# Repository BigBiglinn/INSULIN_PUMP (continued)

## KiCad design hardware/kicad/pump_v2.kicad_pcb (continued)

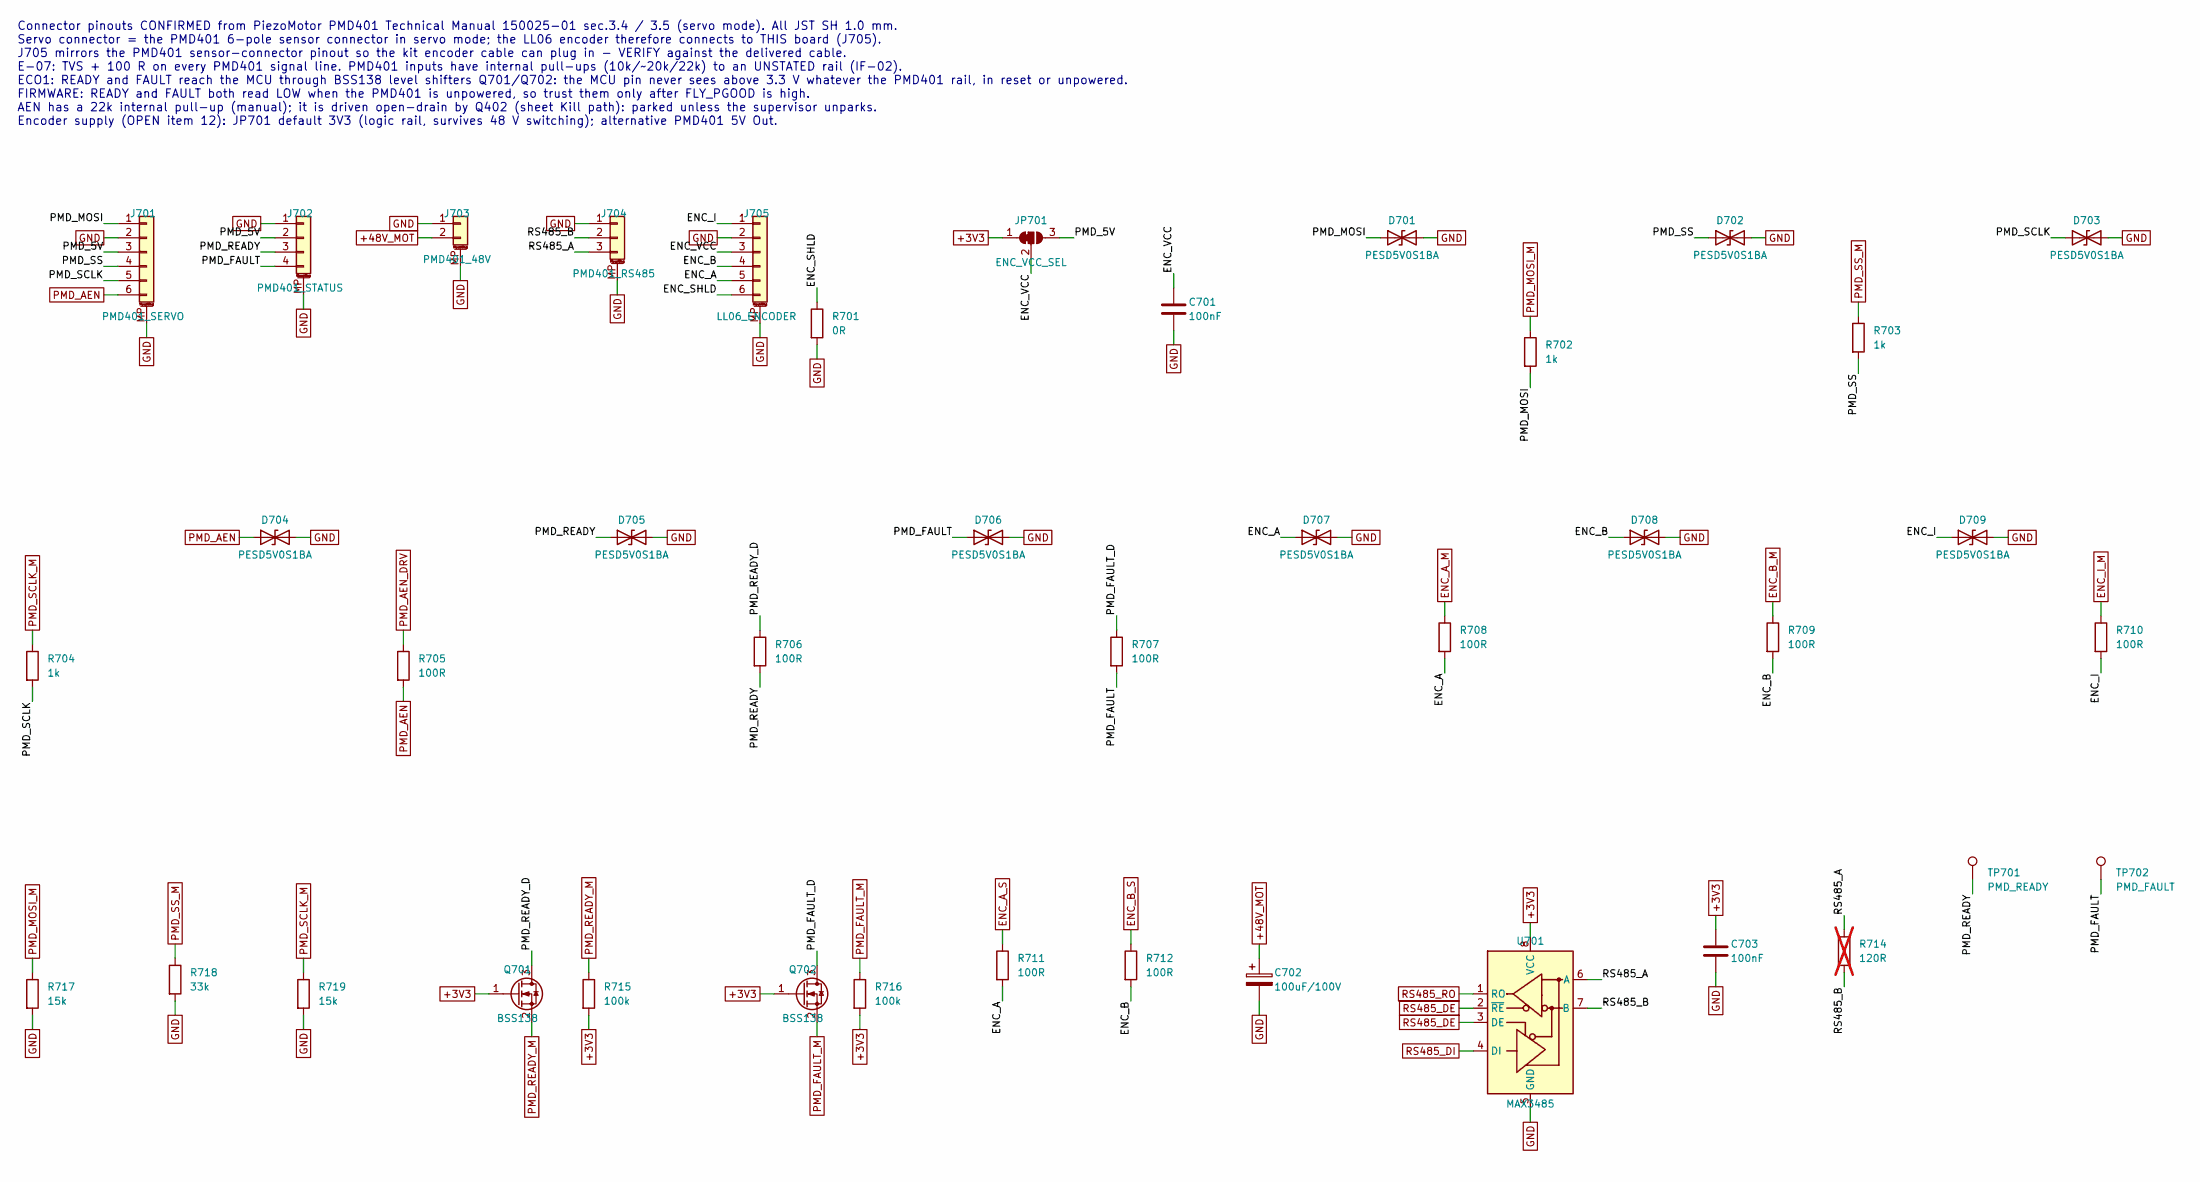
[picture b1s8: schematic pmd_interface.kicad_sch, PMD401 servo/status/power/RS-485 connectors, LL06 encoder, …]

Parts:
C701, C703: 100nF; C_0603_1608Metric
C702: 100uF/100V; CP_Radial_D12.5mm_P5.00mm
D701, D702, D703, D704, D705, D706, D707, D708, D709: PESD5V0S1BA; D_SOD-323; MPN Nexperia PESD5V0S1BA,115
J701: PMD401_SERVO; JST_SH_SM06B-SRSS-TB_1x06-1MP_P1.00mm_Horizontal; MPN JST SM06B-SRSS-TB
J702: PMD401_STATUS; JST_SH_SM04B-SRSS-TB_1x04-1MP_P1.00mm_Horizontal; MPN JST SM04B-SRSS-TB
J703: PMD401_48V; JST_SH_SM02B-SRSS-TB_1x02-1MP_P1.00mm_Horizontal; MPN JST SM02B-SRSS-TB
J704: PMD401_RS485; JST_SH_SM03B-SRSS-TB_1x03-1MP_P1.00mm_Horizontal; MPN JST SM03B-SRSS-TB
J705: LL06_ENCODER; JST_SH_SM06B-SRSS-TB_1x06-1MP_P1.00mm_Horizontal; MPN JST SM06B-SRSS-TB
JP701: ENC_VCC_SEL; SolderJumper-3_P1.3mm_Bridged12_RoundedPad1.0x1.5mm_NumberL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
Q701, Q702: BSS138; SOT-23; MPN BSS138 (e.g. Nexperia BSS138P)
R701: 0R; R_0603_1608Metric
R702, R703, R704: 1k; R_0603_1608Metric
R705, R706, R707, R708, R709, R710, R711, R712: 100R; R_0603_1608Metric
R714: 120R; R_0603_1608Metric; not fitted
R715, R716: 100k; R_0603_1608Metric
R717, R719: 15k; R_0603_1608Metric
R718: 33k; R_0603_1608Metric
TP701: PMD_READY; TestPoint_Pad_D1.0mm
TP702: PMD_FAULT; TestPoint_Pad_D1.0mm
U701: MAX3485; SOIC-8_3.9x4.9mm_P1.27mm; MPN MAX3485 SOIC-8 (suffix TBD)

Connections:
+3V3: C703.1, JP701.1 (A), Q701.1 (G), Q702.1 (G), R715.2, R716.2, U701.8 (VCC); also elsewhere on the board
/PMD401 & encoder interface/ENC_A: D707.1 (A1), J705.5, R708.2, R711.2
/PMD401 & encoder interface/ENC_B: D708.1 (A1), J705.4, R709.2, R712.2
/PMD401 & encoder interface/ENC_I: D709.1 (A1), J705.1, R710.2
/PMD401 & encoder interface/ENC_SHLD: J705.6, R701.1
/PMD401 & encoder interface/ENC_VCC: C701.1, J705.3, JP701.2 (C)
/PMD401 & encoder interface/PMD_5V: J701.3, J702.2, JP701.3 (B)
/PMD401 & encoder interface/PMD_FAULT: D706.1 (A1), J702.4, R707.2, TP702.1
/PMD401 & encoder interface/PMD_FAULT_D: Q702.3 (D), R707.1
/PMD401 & encoder interface/PMD_MOSI: D701.1 (A1), J701.1, R702.2
/PMD401 & encoder interface/PMD_READY: D705.1 (A1), J702.3, R706.2, TP701.1
/PMD401 & encoder interface/PMD_READY_D: Q701.3 (D), R706.1
/PMD401 & encoder interface/PMD_SCLK: D703.1 (A1), J701.5, R704.2
/PMD401 & encoder interface/PMD_SS: D702.1 (A1), J701.4, R703.2
/PMD401 & encoder interface/RS485_A: J704.3, R714.1, U701.6 (A)
/PMD401 & encoder interface/RS485_B: J704.2, R714.2, U701.7 (B)
ENC_A_M: R708.1; also elsewhere on the board
ENC_A_S: R711.1; also elsewhere on the board
ENC_B_M: R709.1; also elsewhere on the board
ENC_B_S: R712.1; also elsewhere on the board
ENC_I_M: R710.1; also elsewhere on the board
PMD_AEN: D704.1 (A1), J701.6, R705.2; also elsewhere on the board
PMD_AEN_DRV: R705.1; also elsewhere on the board
PMD_FAULT_M: Q702.2 (S), R716.1; also elsewhere on the board
PMD_MOSI_M: R702.1, R717.1; also elsewhere on the board
PMD_READY_M: Q701.2 (S), R715.1; also elsewhere on the board
PMD_SCLK_M: R704.1, R719.1; also elsewhere on the board
PMD_SS_M: R703.1, R718.1; also elsewhere on the board
RS485_DE: U701.2 (~RE), U701.3 (DE); also elsewhere on the board
RS485_DI: U701.4 (DI); also elsewhere on the board
RS485_RO: U701.1 (RO); also elsewhere on the board

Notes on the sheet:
Connector pinouts CONFIRMED from PiezoMotor PMD401 Technical Manual 150025-01 sec.3.4 / 3.5 (servo mode). All JST SH 1.0 mm. Servo connector = the PMD401 6-pole sensor connector in servo mode; the LL06 encoder therefore connects to THIS board (J705). J705 mirrors the PMD401 sensor-connector pinout 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

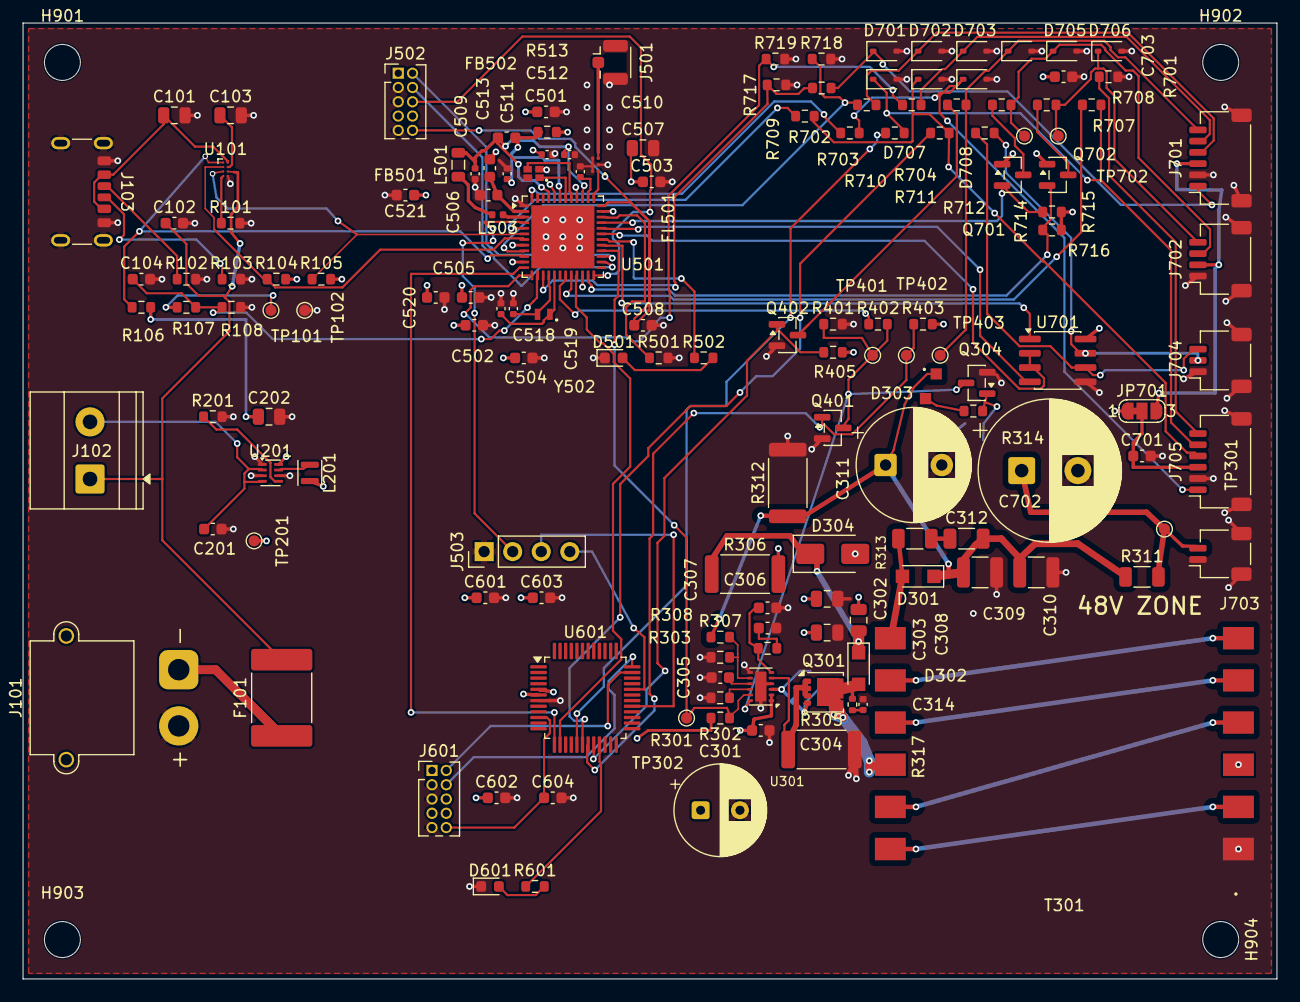
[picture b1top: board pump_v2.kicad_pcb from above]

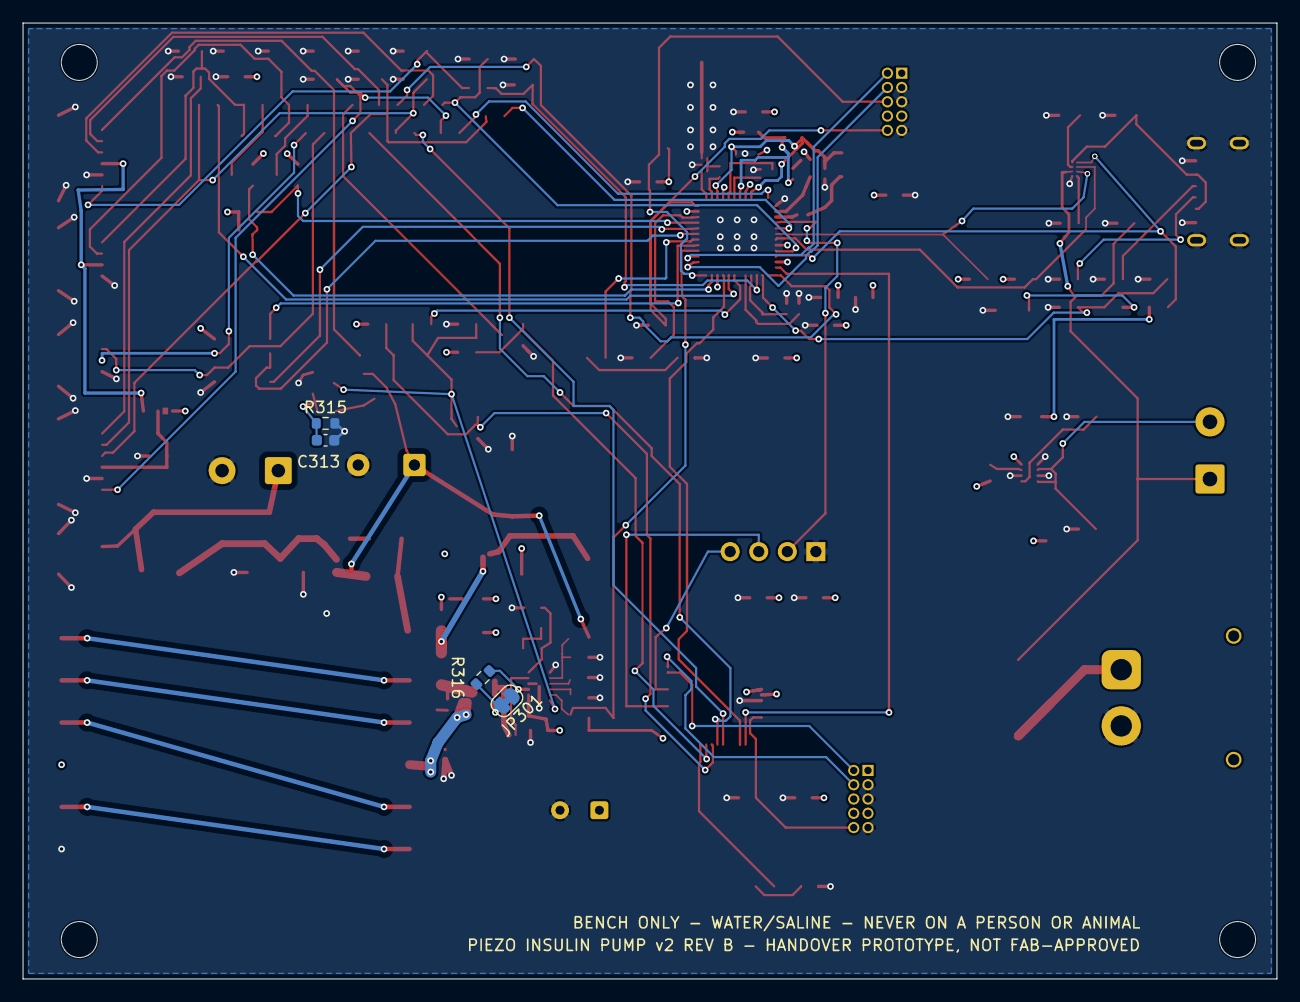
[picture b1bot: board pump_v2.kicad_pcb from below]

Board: 4 copper layers, 111.5 x 85.0 mm, 158 parts (4 on the bottom side), 101 nets.

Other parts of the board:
C313: 10nF; C_0603_1608Metric
C314: TBD; C_0402_1005Metric
D303: BZX84B51; SOT-23_Zener_A1_K3
D304: SMAJ15A; D_SMA
JP301: BRIDGED; SolderJumper-2_P1.3mm_Bridged_RoundedPad1.0x1.5mm
Q304: BSS138; SOT-23
R314: 1k; R_0603_1608Metric
R315: 10k; R_0603_1608Metric
R316: TBD; R_0603_1608Metric
R317: TBD; R_0402_1005Metric

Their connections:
/48V flyback/FLY_CLAMP: D304.1; also elsewhere on the board
/48V flyback/FLY_DSNB: C314.1, R317.2
/48V flyback/OVP_G: C313.1, Q304.1, R314.2, R315.1
/48V flyback/OVP_K: D303.2, R314.1
FLY_EN: Q304.3; also elsewhere on the board

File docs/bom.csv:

"Refs","Value","Footprint","MPN","Status","Qty","DNP"
"C101","2.2uF/25V","Capacitor_SMD:C_0805_2012Metric","","DS","1",""
"C102","1uF/10V","Capacitor_SMD:C_0603_1608Metric","","DS","1",""
"C103,C202","10uF/10V","Capacitor_SMD:C_0805_2012Metric","","DS","2",""
"C104","100nF","Capacitor_SMD:C_0603_1608Metric","","CALC","1",""
"C201","4.7uF/10V","Capacitor_SMD:C_0603_1608Metric","","DS","1",""
"C301","220uF/16V","Capacitor_THT:CP_Radial_D8.0mm_P3.50mm","","DECIDED","1",""
"C302,C303","10uF/10V X5R","Capacitor_SMD:C_0805_2012Metric","","CALC","2",""
"C304","2.2uF/10V","Capacitor_SMD:C_0603_1608Metric","","DS","1",""
"C305","4.7uF/10V X5R","Capacitor_SMD:C_0603_1608Metric","","CALC","1",""
"C306","180nF","Capacitor_SMD:C_0603_1608Metric","","CALC","1",""
"C307","3.3nF","Capacitor_SMD:C_0603_1608Metric","","CALC","1",""
"C308","470nF/50V X7R","Capacitor_SMD:C_0805_2012Metric","","CALC","1",""
"C309,C310","2.2uF/100V X7R","Capacitor_SMD:C_1210_3225Metric","","CALC","2",""
"C311","47uF/100V","Capacitor_THT:CP_Radial_D10.0mm_P5.00mm","","DECIDED","1",""
"C312","100pF/250V C0G","Capacitor_SMD:C_1206_3216Metric","","CALC","1",""
"C501,C502,C503,C504,C505,C506,C508,C601,C602,C604,C701,C703","100nF","Capacitor_SMD:C_0603_1608Metric","","ASSUMED","12",""
"C507,C603","4.7uF","Capacitor_SMD:C_0603_1608Metric","","ASSUMED","2",""
"C509,C510,C511,C512,C513","TBD","Capacitor_SMD:C_0603_1608Metric","","PLACEHOLDER","5",""
"C514,C515,C516,C517,C518,C519","TBD","Capacitor_SMD:C_0402_1005Metric","","PLACEHOLDER","6","DNP"
"C702","100uF/100V","Capacitor_THT:CP_Radial_D12.5mm_P5.00mm","","DECIDED","1",""
"D301","PNE20010ER","Diode_SMD:Nexperia_CFP3_SOD-123W","Nexperia PNE20010ER","DS","1",""
"D302","PMEG10020ELR","Diode_SMD:Nexperia_CFP3_SOD-123W","Nexperia PMEG10020ELR","DS","1",""
"D501","LED_GRN","LED_SMD:LED_0603_1608Metric","","ASSUMED","1",""
"D601","LED_RED","LED_SMD:LED_0603_1608Metric","","ASSUMED","1",""
"D701,D702,D703,D704,D705,D706,D707,D708,D709","TVS_5V_TBD","Diode_SMD:D_SOD-323","","TBD","9",""
"F101","5A","Fuse:Fuse_2920_7451Metric","","TBD","1",""
"J101","BATTERY_1S","Connector_AMASS:AMASS_XT30PW-M_1x02_P2.50mm_Horizontal","AMASS XT30PW-M","ASSUMED","1",""
"J102","MASTER_SW_EXT","TerminalBlock_Phoenix:TerminalBlock_Phoenix_MKDS-1,5-2-5.08_1x02_P5.08mm_Horizontal","","ASSUMED","1",""
"J103","USB_C_PWR","Connector_USB:USB_C_Receptacle_GCT_USB4125-xx-x_6P_TopMnt_Horizontal","GCT USB4125","ASSUMED","1",""
"J501","U.FL","Connector_Coaxial:U.FL_Hirose_U.FL-R-SMT-1_Vertical","Hirose U.FL-R-SMT-1","ASSUMED","1",""
"J502,J601","SWD_10pin","Connector_PinHeader_1.27mm:PinHeader_2x05_P1.27mm_Vertical","","ASSUMED","2",""
"J503","CONSOLE","Connector_PinHeader_2.54mm:PinHeader_1x04_P2.54mm_Vertical","","ASSUMED","1",""
"J701","PMD401_SERVO","Connector_JST:JST_SH_SM06B-SRSS-TB_1x06-1MP_P1.00mm_Horizontal","JST SM06B-SRSS-TB","DS","1",""
"J702","PMD401_STATUS","Connector_JST:JST_SH_SM04B-SRSS-TB_1x04-1MP_P1.00mm_Horizontal","JST SM04B-SRSS-TB","DS","1",""
"J703","PMD401_48V","Connector_JST:JST_SH_SM02B-SRSS-TB_1x02-1MP_P1.00mm_Horizontal","JST SM02B-SRSS-TB","DS","1",""
"J704","PMD401_RS485","Connector_JST:JST_SH_SM03B-SRSS-TB_1x03-1MP_P1.00mm_Horizontal","JST SM03B-SRSS-TB","DS","1",""
"J705","LL06_ENCODER","Connector_JST:JST_SH_SM06B-SRSS-TB_1x06-1MP_P1.00mm_Horizontal","JST SM06B-SRSS-TB","ASSUMED","1",""
"JP701","ENC_VCC_SEL","Jumper:SolderJumper-3_P1.3mm_Bridged12_RoundedPad1.0x1.5mm_NumberLabels","","ASSUMED","1",""
"L201","2.2uH","Inductor_SMD:L_0603_1608Metric","","DS","1",""
"L501","L_SMPS_TBD","Inductor_SMD:L_0805_2012Metric","","PLACEHOLDER","1",""
"L502","TBD","Inductor_SMD:L_0402_1005Metric","","PLACEHOLDER","1",""
"Q301","CSD16340Q3","Package_SON:VSON-8_3.3x3.3mm_P0.65mm_NexFET","TI CSD16340Q3","DS","1",""
"Q302","PMOS_TBD","Package_TO_SOT_SMD:SOT-223-3_TabPin2","","PLACEHOLDER","1","DNP"
"Q303","NMOS_TBD","Package_TO_SOT_SMD:SOT-223-3_TabPin2","","PLACEHOLDER","1","DNP"
"Q401","BSS138","Package_TO_SOT_SMD:SOT-23","BSS138","DECIDED","1",""
"Q402","BSS138","Package_TO_SOT_SMD:SOT-23","BSS138 (e.g. Nexperia BSS138P)","DECIDED","1",""
"R101,R104,R105,R106","10k","Resistor_SMD:R_0603_1608Metric","","DS","4",""
"R102,R103","5.1k","Resistor_SMD:R_0603_1608Metric","","ASSUMED","2",""
"R107,R108","1M 1%","Resistor_SMD:R_0603_1608Metric","","CALC","2",""
"R201","267k 1%","Resistor_SMD:R_0603_1608Metric","","DS","1",""
"R301","73.2k 1%","Resistor_SMD:R_0603_1608Metric","","CALC","1",""
"R302","100k","Resistor_SMD:R_0603_1608Metric","","ASSUMED","1",""
"R303","3.01k 1%","Resistor_SMD:R_0603_1608Metric","","CALC","1",""
"R305","22m 1% 1W","Resistor_SMD:R_2512_6332Metric","","CALC","1",""
"R306","220R 1W","Resistor_SMD:R_2512_6332Metric","","CALC","1",""
"R307","470k 1%","Resistor_SMD:R_0603_1608Metric","","CALC","1",""
"R308","10k 1%","Resistor_SMD:R_0603_1608Metric","","CALC","1",""
"R309,R310","TBD","Resistor_SMD:R_0603_1608Metric","","PLACEHOLDER","2","DNP"
"R311","0R","Resistor_SMD:R_1206_3216Metric","","ASSUMED","1",""
"R312","TBD","Resistor_SMD:R_2512_6332Metric","","PLACEHOLDER","1","DNP"
"R313","220R 1206","Resistor_SMD:R_1206_3216Metric","","CALC","1",""
"R401","4.7k","Resistor_SMD:R_0603_1608Metric","","DECIDED","1",""
"R402","1k","Resistor_SMD:R_0603_1608Metric","","DECIDED","1",""
"R403,R405","10k","Resistor_SMD:R_0603_1608Metric","","DECIDED","2",""
"R501","10k","Resistor_SMD:R_0603_1608Metric","","ASSUMED","1",""
"R502,R601","1k","Resistor_SMD:R_0603_1608Metric","","ASSUMED","2",""
"R510,R511,R512,R513","0R_VERIFY","Resistor_SMD:R_0603_1608Metric","","PLACEHOLDER","4","DNP"
"R701","0R","Resistor_SMD:R_0603_1608Metric","","ASSUMED","1",""
"R702,R703,R704,R705,R706,R707,R708,R709,R710,R711,R712","100R","Resistor_SMD:R_0603_1608Metric","","DECIDED","11",""
"R714","120R","Resistor_SMD:R_0603_1608Metric","","ASSUMED","1","DNP"
"T301","XFMR_TBD","pump_v2:XFMR_PLACEHOLDER_4P","","PLACEHOLDER","1",""
"U101","BQ25188YBGR","pump_v2:TI_YBG0008_DSBGA-8_P0.4mm","BQ25188YBGR","DECIDED","1",""
"U201","TPS62840DLCR","Package_SON:Texas_VSON-HR-8_1.5x2mm_P0.5mm","TPS62840DLCR","DECIDED","1",""
"U301","LM51551DSSR","Package_SON:WSON-12-1EP_3x2mm_P0.5mm_EP1x2.65","LM51551DSSR","DECIDED","1",""
"U501","STM32WBA55CGUx","Package_DFN_QFN:QFN-48-1EP_7x7mm_P0.5mm_EP5.6x5.6mm","STM32WBA55CGU6 (temp suffix TBD)","DECIDED","1",""
"U601","STM32C031C6Tx","Package_QFP:LQFP-48_7x7mm_P0.5mm","STM32C031C6T6 (package ASSUMED)","DECIDED","1",""
"U701","MAX3485","Package_SO:SOIC-8_3.9x4.9mm_P1.27mm","MAX3485 SOIC-8 (suffix TBD)","DECIDED","1",""
"Y501","32MHz_TBD","Crystal:Crystal_SMD_2016-4Pin_2.0x1.6mm","","TBD","1",""
"Y502","32.768kHz","Crystal:Crystal_SMD_3215-2Pin_3.2x1.5mm","","PLACEHOLDER","1","DNP"

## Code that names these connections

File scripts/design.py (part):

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          {"1": "VBAT", "2": "VBAT", "12": "FLY_EN", "10": "FLY_RT", "9": "FLY_SS", "11": "FLY_PGOOD",
           "3": "FLY_GATE", "5": "FLY_CS", "8": "FLY_FB", "6": "FLY_COMP", "4": "GND", "7": "GND", "13": "GND"},
          status="DECIDED", mpn="LM51551DSSR",
          note="K-12. Pinout SNVSB75E Table 7-1. BIAS=VCC (SNVSB75E sec.1: 2.97-16 V). UVLO/EN max = VBIAS+0.3 V; FLY_EN <= 0.82 x 3V3 <= VBAT")
    C(s, "C304", "2.2uF/10V", "VBAT", "GND", status="DS",
      note="VCC/BIAS bypass to PGND: SNVSB75E 'recommended VCC capacitor value is from 1 uF to 4.7 uF'")
    R(s, "R301", "73.2k 1%", "FLY_RT", "GND", status="CALC",
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                   "On Rev B the enable node is LM51551 UVLO/EN (FLY_EN). EN rising threshold 0.4-0.7 V, UVLO 1.425-1.575 V (SNVSB75E).\n"
                   "MCU high: 3.3 V x 4.7/(4.7+1) = 2.72 V -> run.  Pull-down only: 0 V -> shutdown.  BSS138 on: ~0 V -> shutdown.\n"
                   "Veto default (owner decision 10 Oct 2026, OPEN item 3 closed): R403 10k PULL-UP fitted -> veto ON whenever the supervisor\n"
                   "is in reset, crashed with its pin high/high-Z, or not running; firmware must drive PB0 LOW to permit 48 V. (R404 removed.)\n"
                   "PMD401 park (owner decision 10 Oct 2026, OPEN item 4): open-drain Q402 BSS138 with R405 10k gate PULL-UP -> AEN held LOW\n"
                   "(parked) by default; the PMD401's own 22k pull-up provides the run level, so no 3.3/5 V level question. Supervisor drives\n"
                   "PB1 (SUP_PARK) LOW to unpark. BSS138 VGS(th) 0.9-1.5 V (Nexperia BSS138P datasheet). SG-03/SG-05 still required on hardware.")
    R(s, "R401", "4.7k", "FLY_EN", "GND", status="DECIDED", note="K-10 enable pull-down (fail-off default)")
    R(s, "R402", "1k", "MCU_48V_EN", "FLY_EN", status="DECIDED", note="K-10 main MCU drive resistor so the supervisor can overpower it")
    s.add("Q401", "Transistor_FET:BSS138", "BSS138", {"1": "SUP_VETO", "2": "GND", "3": "FLY_EN"},
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          "Package_TO_SOT_SMD:SOT-23", status="DECIDED", mpn="BSS138 (e.g. Nexperia BSS138P)",
          note="Owner 10 Oct 2026: open-drain AEN driver. ON (gate high) = AEN low = motor parked. Sinks only the PMD401 22k pull-up")
    R(s, "R405", "10k", "SUP_PARK", "+3V3", status="DECIDED",
      note="Owner 10 Oct 2026: Q402 gate pull-UP -> parked by default; supervisor PB1 LOW unparks")
    TP(s, "TP401", "FLY_EN")
    TP(s, "TP402", "SUP_VETO")
    TP(s, "TP403", "PMD_AEN")
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    s = Sheet("Main MCU STM32WBA55", "mcu_main.kicad_sch", "Main MCU STM32WBA55CG: dosing, BLE, encoder, PMD401 SPI")
    sheets.append(s)
    s.notes.append("Pin map DERIVED from ST pin data in the KiCad STM32WBA55CGUx symbol; CONFIRM IN STM32CubeMX before layout freeze.\n"
                   "Encoder on TIM2 CH1/CH2 (PB6/PA8) - TIM2 width must be confirmed in RM0493 (CF-21/FW-08).\n"
                   "SPI3 -> PMD401 (mode 3, <= 500 kbit/s, PMD401 manual 150025-01 sec.5.2). USART2 + DE -> MAX3485. LPUART1 <-> supervisor link.\n"
                   "USART1 TX-only console (PA8, the only USART1_RX pin, carries the encoder).\n"
                   "ECO1: supplies per DS14127 Figure 15 (SMPS scheme), AN6373 and MB1803 B-01. VDDRFPA on the SMPS output limits TX to about +3 dBm (AN6373 sec.7);\n"
                   "for +10 dBm fit R513 and remove FB502. RF: MLPF-WB-04D3 with a 63 ohm line from pin 37 and a 50 ohm line to J501. HSE and LSE per AN5948 Table 5.")
    nm = {
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      note="ECO1. AN6373 sec.4: 2.2 uH +/-20 %, RDC < 500 mohm, Iop > 200 mA, Isat > 800 mA; other values not stable")
    C(s, "C509", "4.7uF", "WBA_VDD11", "GND", FP_C0402, status="DS", mpn="Murata GRM155R60J475ME47D",
      note="ECO1. SMPS output cap, fixed by design: 4.7 uF +/-20 %, ESR < 50 mohm (AN6373 sec.4.3)")
    C(s, "C510", "470nF", "WBA_VDDHPA", "GND", FP_C0402, status="DS", note="ECO1. VDDHPA: capacitor only, no supply (DS14127 sec.3.12). At pin 38")
    C(s, "C511", "100nF", "WBA_VDD11", "GND", FP_C0402, status="DS", note="ECO1. VDDANA pin 39 on the VDD11 node (DS14127 sec.3.12, Fig.15). At pin 39")
    C(s, "C512", "100nF", "+3V3", "GND", FP_C0402, status="DS", note="ECO1. VDDRF pin 40 on VDD (DS14127 sec.3.12). At pin 40")
    C(s, "C513", "100nF", "WBA_VDDRFPA", "GND", FP_C0402, status="DS", note="ECO1. VDDRFPA pin 43 (DS14127 Fig.15). At pin 43")
    s.add("FB502", "Device:FerriteBead", "47R@100MHz", {"1": "WBA_VDD11", "2": "WBA_VDDRFPA"}, FP_C, status="DS", mpn="Taiyo Yuden LSMGA160808T470RG",
          note="ECO1. VDDRFPA from the SMPS output; AN6373 sec.7 filter, as MB1803 L7. Remove if R513 is fitted")
    # WBA55 rails fed through a bead/inductor or by the chip's own SMPS: no pin on these nets is a
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          note="ECO1. Fitted: AN5948 Table 5, radio sleep clock and RTC. Land from ST MB1803. Beside pins 16/17. Do not toggle PC13 (ES0592 sec.2.2.10)")
    C(s, "C518", "6pF C0G", "LSE_IN", "GND", FP_C0402, status="DS", note="ECO1. MB1803 C9, matched to the NX1610SE (AN5948 Fig.14)")
    C(s, "C519", "6pF C0G", "LSE_OUT", "GND", FP_C0402, status="DS", note="ECO1. MB1803 C8, matched to the NX1610SE (AN5948 Fig.14)")
    R(s, "R501", "10k", "MAIN_BOOT0", "GND", status="ASSUMED", note="PH3-BOOT0 strap low = boot from flash (RM0493). MB1803 uses 100k; either works")
    R(s, "R502", "1k", "LED_MAIN", "LED_MAIN_A", status="ASSUMED", note="Status LED (debug aid)")
    s.add("D501", "Device:LED", "LED_GRN", {"2": "LED_MAIN_A", "1": "GND"}, FP_LED, status="ASSUMED", note="Main MCU status LED (debug aid)")
    SWD(s, "J502", "MAIN", swo=True)
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    sheets.append(s)
    s.notes.append("K-6 / F-09: separate MCU, separate code base. It can only STOP: veto on the 48 V enable (SUP_VETO) and park line (PMD_AEN).\n"
                   "S-07 (approved 10 Oct): encoder A/B also into TIM3 CH1/CH2 via its own series resistors.\n"
                   "Pin map DERIVED from the KiCad STM32C031C6Tx symbol (ST pin data); CONFIRM in CubeMX. NRST assumed on PF2 (PF2-NRST) - VERIFY.\n"
                   "Package LQFP48 (C6T6) ASSUMED; the C031C6 also exists in UFQFPN48 (C6U6).")
    nm = {"6": "+3V3", "5": "+3V3", "7": "GND", "10": "SUP_NRST", "35": "SUP_SWDIO", "36": "SUP_SWCLK",
          "13": "HB_S2M", "14": "HB_M2S", "29": "CON_SUP_TX", "32": "CON_SUP_RX",
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    for rref, net, val in (("R717", "PMD_MOSI_M", "15k"), ("R718", "PMD_SS_M", "33k"), ("R719", "PMD_SCLK_M", "15k")):
        R(s, rref, val, net, "GND", status="CALC",
          note="ECO2. Divider with the PMD401 pull-up: holds the pin below 4 V if VDD is 0 while the PMD401 rail decays (DS14127 Table 27). 3.6 V max at a 5.25 V rail with -30 % pull-up")
    for qref, rref, pin_net, drain in (("Q701", "R715", "PMD_READY_M", "PMD_READY_D"), ("Q702", "R716", "PMD_FAULT_M", "PMD_FAULT_D")):
        s.add(qref, "Transistor_FET:BSS138", "BSS138", {"1": "+3V3", "2": pin_net, "3": drain},
              "Package_TO_SOT_SMD:SOT-23", status="DS", mpn="BSS138 (e.g. Nexperia BSS138P)",
              note="ECO1. Non-inverting level shifter: gate +3V3, source MCU, drain PMD401 side. VGS(th) 0.9-1.5 V. Off when +3V3 is down, so the pin is isolated")
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
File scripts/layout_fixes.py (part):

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
Applies, in order, to the board at the checkpoint tag `checkpoint/pre-layout-fixes-2026-10-31`:
  1. +48V_MOT: R311.2 -> J703.2 on F.Cu and C702.1 -> that route on B.Cu (HV48 0.4 mm track).
  2. U301 soft-start: C305 moved north of U301; FLY_SS routed pin 9 -> C305.1; AGND pin 7 tied to the
     exposed pad (SNVSB75E 10.5.1); FLY_FB / FLY_RT / FLY_PGOOD escapes re-routed to make room.
  3. TP302 moved from the J703 area onto the FLY_PGOOD trace beside U301/R302.
  4. Router-found connections (pcbroute.py, deterministic A*), each accepted only with zero
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

def step_console(S):
    """Move J503 (4-pin console header: GND, CON_MAIN_TX, CON_SUP_TX, CON_SUP_RX) from the top edge to the
    free area between the two MCUs, then route its three signal nets."""
    mtx = [i for i in S.b.items if i.kind == "track" and short(i.net) == "CON_MAIN_TX" and i.layers[0] == "B.Cu"]
    S.remove(mtx, "CON_MAIN_TX run to the old J503 position")
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
def step_signals(S):
    a, rest = comp_split(S, "R711", "1")
    routed(S, "ENC_A_S (R711.1 -> U601.17 PA6)", a, rest)
    a, rest = comp_split(S, "U501", "28")
    routed(S, "FLY_PGOOD (U501.28 PA12 -> U301/R302/TP302)", a, rest)


def main():
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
